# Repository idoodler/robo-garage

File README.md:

# Robo-Garage

Kitchen cabinet garage for a **Dreame L10s Pro Ultra Heat** robot vacuum.
ESP32 + ESPHome + Home Assistant: motorised door, light barrier, reed contacts, fan, LED ring, temperature/humidity, water leak probe + valve, buzzer.

**Live simulator:** https://claude.ai/artifact/KapGY8dMDmhuJijCuEXQXC

## Versions

| Part | Version | Status |
|---|---|---|
| Controller PCB | v1.3.1 | DRC 0 errors / 0 warnings (KiCad 7). JLCPCB assembles all parts (SMD + clamps), only the DevKitC is plugged in (USB-C reachable from outside). Power headroom: 12 V in 6 A, actuator 4.9 A limit, valve 3 A, every power path checked against IPC-2221. v1.3.1: clamp pins in 2 rows like the real part, pick & place rotations computed from JLC's own footprints |
| Case | v1.3.1 | fits PCB v1.3.1 (0 mm³ overlap with the part stand-in), DevKit USB-C through the left wall |
| ESPHome config | – | checked with ESPHome 2026.10.2. Set in HA without reflashing: beam type, actuator type (with / without built-in limit switches), open / close time, motor current threshold, stall current; "Door motor fault" when a move draws no current. Light barrier: retroreflective NPN sensor (E3Z-R61 type, Light-ON) + reflector on the BEAM clamp, blue wire on TX− so the self-test can switch it off (no PCB change). Line LED: SK6812 RGBW 144/m, 72 LEDs, capped at 25 % per channel (≤ 1.44 A of the 1.5 A LED output) |
| Simulator | v5.6 | door open slider for all 4 door types, printed door parts (doors v2.2) in 3D + side view, door downloads, retroreflective light barrier with its reflector, Line LED with 72 SK6812 RGBW LEDs |
| Doors | v2.2 | Printed parts for all 4 door types (lift door, flap out, up & over, parallel lift), no supports. Up & over + parallel lift: print-in-place modules with hourglass joints and hollow pins, skeleton plates and arms checked by 3D FE as printed (`check_strength.py`): 12 % less filament than v2.1 (both module pairs together), the most loaded spot down from 1.35 to 0.87 of its allowable at a 100 N stall (calculated), checked over the whole travel (joint gap 0.45 mm, up & over peg in its track 0.4 mm, other gaps ≥ 1 mm). Parallel lift parks 23 mm out (40 mm max) |

## Folders

| Folder | What is inside |
|---|---|
| `esphome/` | ESPHome config for the board (needs `secrets.yaml` with `wifi_ssid`, `wifi_password`) |
| `homeassistant/` | Home Assistant blueprint `robo-garage.yaml`: door follows the robot vacuum, clean button, button ring + status LED, rear fan drying, iOS Live Activities, messages (see below) |
| `pcb/gen/` | PCB generator (Python + KiCad `pcbnew`). `parts.py` = single source of truth, `fplib.py` makes the own footprints (`pcb/lib/robo.pretty`) |
| `pcb/robo-garage/` | Work folder. Only `robo-garage.ses` (Freerouting result) is in git |
| `pcb/out/` | Order files: gerbers zip, BOM + CPL for JLCPCB, KiCad project, renders, `pin1-check.png`. **Order guide: `pcb/out/README.md`** |
| `case/` | 3D-printed case: OpenSCAD source, STL files, pictures, print guide |
| `doors/` | Printed door parts for all 4 door types: OpenSCAD source, STL files, check scripts, print + assembly guide (`doors/README.md`) |
| `simulator/` | Simulator web page: `robo-garage.html` (source) → `build_page.py` → `index.html` |

## Build

GitHub Actions runs all of this on every push (`.github/workflows/build.yml`).
Locally: run from the repo root. Tested with KiCad 7.0.11 (Python `pcbnew`), Python 3 + shapely 2.2, OpenSCAD 2021.01.

| Step | Command |
|---|---|
| PCB: bare board | `python3 pcb/gen/build.py` |
| PCB: tracks + GND pour + DRC | `python3 pcb/gen/finish.py` (stops with an error on any DRC issue) |
| PCB: gerbers, BOM, CPL, renders | `python3 pcb/gen/fab.py pcb/robo-garage/robo-garage_routed.kicad_pcb pcb/out` |
| PCB: copy to `pcb/out` + zip | `pcb/gen/package.sh` |
| PCB: re-route (optional) | `pcb/gen/pipeline.sh` (Freerouting is not deterministic: run it again if `finish.py` reports unconnected items) |
| Case: PCB data, STL, zip | `case/build.sh` |
| Doors: STL, zip | `doors/build.sh` (other joint gap: `doors/build.sh -D cj=0.35`) |
| Doors: motion, gap and overhang checks | `python3 doors/check_parallel.py`, `python3 doors/check_upover.py`, `python3 doors/check_simple.py` |
| Doors: strength (joint loads + 3D FE as printed, about 6 min on 32 cores, up to 48 GB; `--jobs=1` for less) | `python3 doors/check_strength.py` (misuse case: `--yank`) |
| Simulator page | `python3 simulator/build_files.py` (downloads, pictures, case + door GLB) then `python3 simulator/build_page.py` |
| Flash ESP32 | `esphome run esphome/robo-garage-pcb.yaml` |

| Tool | Needed for |
|---|---|
| Python packages `shapely` 2.2, `segno` 1.6 (QR code on the silkscreen) | `build.py`, `finish.py` |
| `kicad-cli`, `rsvg-convert`, Python package `Pillow` | `fab.py` |
| `zip` | `package.sh`, `case/build.sh`, `doors/build.sh` |
| `openscad`, font DejaVu Sans | `case/build.sh`, `doors/build.sh`, `simulator/build_files.py` |
| Python packages `trimesh`, `rtree`, `shapely`, `numpy`; `xvfb-run` for `render.py`; `scipy`, `pyamg` for `check_strength.py`; `matplotlib` for `paper_template.py` (run by `doors/build.sh`) | `doors/check_*.py`, `doors/render.py`, `doors/paper_template.py` |
| Python packages `Pillow`, `trimesh`, `numpy`, `shapely`, `fast-simplification` | `simulator/build_files.py` |
| Java, `xvfb-run`, `pcb/tools/freerouting-1.9.0.jar` ([Freerouting releases](https://github.com/freerouting/freerouting/releases)) | `pipeline.sh` only |

Moved a part in `parts.py`? Then the old tracks no longer fit: run `pcb/gen/pipeline.sh` and commit the new `pcb/robo-garage/robo-garage.ses`.

## Home Assistant

Blueprint `homeassistant/robo-garage.yaml` (HA 2026.7 or newer). Import it: *Settings → Automations & scenes → Blueprints → Import blueprint*, URL
`https://github.com/idoodler/robo-garage/blob/main/homeassistant/robo-garage.yaml`, then *Create automation* and pick the robot vacuum and the Robo-Garage entities.

| What happens | How |
|---|---|
| Robot leaves the dock or starts returning | door opens; not open within the time limit or a door motor fault → robot paused + message. Dreame mop wash / drying after the job (reports "cleaning" while docked) keeps the door shut |
| Robot back in the dock, job over, for 1 min (set it) | door closes; beam blocked → the controller reopens, the blueprint waits for a clear beam and tries again (3×), then a message. Dreame: waits while the job still runs in the dock (mop washing, recharge) |
| Clean button | robot docked → door opens, then the robot starts (not on a door motor fault). Robot out → sent home (or paused / nothing) |
| Button ring | on while the robot is parked (brightness set it, 0 = off), pulses during a job in the dock, blinks on a problem |
| Status LED (optional) | red strobe = problem, orange chase = door moving, blue bar = job progress ("Progress" effect + "Status LED progress" number), spinner = returning, pulse = washing / charging in the dock, green = done (2 min), dim pulse = mop wash after the job |
| Water leak, beam fault, motor fault, stall, supply low, robot error | message to the notify entities you pick, else a notification in HA |
| Rear fan | after parking (door closed): fan at 60 % for 60 min (set both, 0 % = off), then back to "Vent auto". Stops early when the robot leaves |
| iOS Live Activities (optional, pick the phones; English or German) | cleaning job: a bar per room, current room + %, phase (mop wash, to the station, ...), door opening / closing, then done / stopped / error; outside a job the door status. Problems: one red list of every robot, station and garage problem, "✅ Problem solved" when all are clear. Made for the Dreame integration (task status, state, current room, progress, error, station sensors + a text and a toggle helper) |
| HA or controller restart | door put back where it belongs |
| Optional | close the door while the robot is out (opens again on "returning"); keep the door open while the drawer is out |

The safety work stays in the firmware: beam stop, stall stop, leak valve.

## Release

| Step | What to do |
|---|---|
| 1 | Set the versions: `VERSION` in `pcb/gen/parts.py` (also printed on the board), `version` in `case/robo-garage-case.scad` |
| 2 | Push to `main` → GitHub Actions builds everything and checks the DRC |
| 3 | Push a tag: `git tag v1.3.1 && git push origin v1.3.1` → GitHub Actions publishes the release with both zips |
| or | On github.com: *Releases* → *Draft a new release* → new tag `v1.3.1` → *Publish*. The zips get attached about 2 min later |

Every build also keeps both zips for 30 days: *Actions* → run → *Artifacts*.

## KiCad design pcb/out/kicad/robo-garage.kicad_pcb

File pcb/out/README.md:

# Robo-Garage controller PCB v1.3.1

100 × 100 mm, 2 layers, 1 oz copper, all parts on top. Made with KiCad 7 + Freerouting (FOSS). DRC: 0 errors, 0 warnings, 0 unconnected.
**Every BOM line has an LCSC number (all in stock, checked 3 Nov 2026) → JLCPCB assembles the whole board (SMD + clamps, sockets, fan header). You only plug in the DevKitC.**

**New in v1.3.1: fit + orientation fixes**
| Fix | v1.3 | v1.3.1 |
|---|---|---|
| KF250 clamps (9 ×) | all pins in one row | **2 pin rows 5 mm apart (zig-zag)**, as on the real part (datasheet + JLC footprint). The v1.3 clamps would not have fitted |
| Pick & place rotation | package rules | **computed from JLC's own footprint of each part** (`pcb/gen/jlc_footprints.json`); the build stops if a part fits no rotation |
| Rotation corrected | – | U2, U3 (pin 1 corner), Q6 (90°), C13 (polarity), BZ1 (− lead was on a dummy pad), J6 (latch peg), J3 / J4 / J15 (90°) |
| Fan header J6 peg hole | Ø1.10 (KiCad stock) | **Ø1.25** as on the Molex drawing |

**New in v1.3: power headroom**
| Area | v1.2 | v1.3 |
|---|---|---|
| 12 V input | 3 A, 2-pole clamp, PTC 2.6 A, AO3407A | **6 A**, 4-pole clamp (2 × 12V, 2 × GND), PTC 7 A (2920), P-FET AO4407C (11.5 mΩ), TVS SMAJ15A |
| Actuator | DRV8871, limit 1.9 A | **DRV8874** (6 A peak), current limit **4.9 A** (R5 = 1.5 kΩ), 3 A moves |
| Motor current | 0.1 Ω shunt, INA219 range 3.2 A | 20 mΩ / 2 W shunt with Kelvin taps, INA219 range 8 A |
| Valve | AO3400A, PTC 1.5 A → max 1.2 A | **IRLTS6342** (30 V, 8.3 A), PTC 4 A (1812) → **max 3 A** |
| 12 V aux | direct from the rail | own PTCs: F7 1.1 A (fan, beam, leak), F8 0.2 A (button LED) |
| LED 5 V | PTC 1.5 A | PTC 2 A |
| T/H sensor | SHT40 | SHT41 (same footprint, address 0x44) |
| Copper | 1.0–1.5 mm | every power path checked against IPC-2221 (table below) |

## Limits (also printed on the back)
| Output | Limit | Protection |
|---|---|---|
| 12 V IN | 6 A continuous (board ≤ 40 °C). PSU 12 V / 5 A recommended, a 3 A PSU still works | F1 PTC 7 A hold / 14 A trip, reverse-polarity P-FET, TVS 15 V |
| ACTUATOR | 3 A moving, **4.9 A hardware limit** | DRV8874 current regulation + over-current + thermal shutdown, INA219 stall stop (firmware) |
| VALVE | 12 V, **3 A** continuous, inductive OK | F4 PTC 4 A hold (≈ 3.2 A at 50 °C), SS34 flyback |
| LED 5 V | 1.5 A (16 WS2812 at full white ≈ 1 A; Line: 72 SK6812 RGBW capped at 25 % in ESPHome ≈ 1.44 A) | F2 PTC 2 A |
| 5 V rail total | 3 A | LMR51430 current limit + hiccup |
| FAN + BEAM + LEAK 12 V | 1.1 A together | F7 1.1 A, F3 / F5 0.2 A per sensor feed |
| BUTTON LED 12 V | 0.2 A | F8 0.2 A |
| LEAK 3V3 | 50 mA | F6 0.2 A (shares the DevKit regulator) |
| Clamps | 5 A per pole, 0.2–0.75 mm² | – |

## Copper check (IPC-2221, outer layer, 1 oz)
DC network solve over every track and via of each power net, current = the limit above. Need = IPC-2221 width for ≤ 20 °C rise.
| Path | Current | Copper (narrowest) | Need | Drop |
|---|---|---|---|---|
| 12V IN → F1 → Q1 | 7 A | 3.0 / 4.2 mm | 2.9 mm | 20 mV |
| Q1 → shunt (west trunk) | 4.9 A | 2.0 mm | 1.8 mm | 81 mV |
| Q1 → valve PTC (east branch) | 4 A | 2.0 mm | 1.3 mm | 21 mV |
| Shunt → DRV8874 VM | 4.9 A | 2.0 mm | 1.8 mm | 67 mV |
| DRV8874 → ACTUATOR clamp | 4.9 A | 1.8 mm (spots of 1.5–1.6 mm: M− 12 mm, M+ 4 mm in total) | 1.8 mm | 44 / 66 mV |
| VALVE 12V / VLV | 4 A | 1.5 mm | 1.3 mm | 24 / 15 mV |
| Buck input | 1.5 A | 0.8 mm | 0.4 mm | 29 mV |
| 5 V buck → LED clamp | 2 A | 0.8 mm | 0.5 mm | 90 mV |
| Aux 12 V (fan, beam, leak) | 1.1 A | 0.6 mm | 0.2 mm | 96 mV |
| Vias in power paths | ≤ 1.1 A | 0.4–0.6 mm drill | 1.3 A per via | – |

Pin necks: 0.4–0.6 mm for ≤ 1.4 mm at the 0.65 mm-pitch DRV8874 pins and the buck SW pin (set by the pin pitch; the wide copper starts right after the pad).
At 4.9 A the 1.5 mm spots run ≈ 26 °C above ambient when held for minutes; a door move takes ≤ 15 s and runs at ≈ 3 A (≈ 10 °C).

## Part checks (datasheets)
| Part | Check | OK |
|---|---|---|
| DRV8874PWPR (U1) | VM 4.5–37 V, 6 A peak, 200 mΩ HS+LS. 3 A → 1.8 W for ≤ 15 s per move; a stall at 4.9 A ends in the firmware stall stop or the driver's thermal shutdown | ✓ |
| LMR51430XFDDCR (U4) | 500 kHz FPWM, 4.5–36 V in, 3 A. TI 12 → 5 V example: 6.8 µH + 44 µF → board: 6.8 µH (Isat 6 A) + 3 × 22 µF. EN tied to VIN through 100 k (allowed) | ✓ |
| INA219 (U2) | Bus ≤ 26 V; the TVS keeps surges ≤ 24.4 V | ✓ |
| IRLTS6342 (Q6) | 30 V, 8.3 A, Vgs ±12 V (driven at 3.3 V): 0.2 W at 3 A | ✓ |
| AO4407C (Q1) | 30 V, 14 A, Vgs ±25 V (BZT52C12 clamps it to 12 V): 0.4 W at 6 A | ✓ |
| R6 20 mΩ 2 W | 0.48 W at 4.9 A | ✓ |
| R44 10 Ω 1206 | ≈ 0.19 W while the buzzer sounds (0.25 W part) | ✓ |
| Electrolytics | C1 / C3 25 V on 12 V, C13 16 V on 5 V | ✓ |
| PTCs | voltage rating ≥ rail: F1 24 V, F4 16 V, F3/F5–F8 30 V on 12 V; F2 12 V on 5 V | ✓ |

## Files
| File | Use |
|---|---|
| `robo-garage_gerbers_JLCPCB.zip` | Upload at JLCPCB (PCB) |
| `robo-garage_BOM_JLCPCB.csv`, `robo-garage_CPL_JLCPCB.csv` | PCB Assembly: BOM + pick & place (48 lines, 114 parts) |
| `pin1-check.png` | Cyan ring = our pin 1 / + / cathode, magenta dot = where JLC puts it (its footprint turned by the CPL rotation). Every dot sits in its ring; compare with JLC's placement preview |
| `orientation.txt` | CPL rotation of every polarised part and the JLC footprint it was computed from |
| `robo-garage-pcb.yaml` | ESPHome config for this board |
| `kicad/` | KiCad project to edit later |
| `render_top.png`, `render_bottom.png` | Pictures |

## Order at JLCPCB
| Step | Setting |
|---|---|
| 1 PCB | Upload the gerbers zip → 2 layers, 1.6 mm, LeadFree HASL, **1 oz**, via covering *Tented*, "Mark on PCB": default. The C-shaped slot around the SHT41 (bottom right) is intended (heat isolation): confirm if JLC asks |
| 2 Assembly | **Economic**, top side, 2 boards, **Tooling holes: Added by Customer** (TH1–TH3 are on the board), *Confirm Parts Placement* = yes |
| 3 Files | Upload BOM + CPL. Parts list: all 48 lines must match by LCSC number (0 "no part selected") |
| 4 THT | The clamps, the 3 sockets and the fan header are THT: keep them ticked → JLC solders them (≈ $3.5 + $0.02 per joint, 96 joints per board) |
| 5 Preview | Compare the placement preview with **`pin1-check.png`**: JLC's pin-1 dot / + / cathode mark must sit in the cyan ring of every U, Q, D, LED, C1, C3, C13, BZ1 and J. The CPL already uses JLC's own footprints (`orientation.txt`), so nothing should need turning. Clamps: wire entry towards the board edge. If JLC's engineers ask about polarity (*Confirm Parts Placement*), answer with `pin1-check.png` |
| 6 Price | ≈ 26 "extended" part types (≈ $3 loading fee each, once per order) – normal for a board like this |

Out of stock? U1 → DRV8874QPWPRQ1 (C22448174, same pinout). U5 → SHT40-AD1F-R2 (C7461846) or SHT41-AD1F-R2 (C7461862), same address, with PTFE cap. KF250 clamp → same footprint family DG250-3.5 / WJ250-3.5 (check the drawing: Ø1.2 holes, 3.5 mm pole pitch, 2 pin rows 5.0 mm apart, odd poles 2.2 mm from the rear face), or leave that line out and hand-solder. Any substitute part needs its JLC footprint in `pcb/gen/jlc_footprints.json` (the build says so). PTCs → same size, hold current and at least the same voltage.

## Parts to buy separately
| Part | Qty | Where it goes |
|---|---|---|
| ESP32 DevKitC V4, **WROOM** (not WROVER: GPIO16/17 are used), board 1.1 in (28 mm) or 1.0 in (25.4 mm) wide – not the narrow 0.9 in clone | 1 | Plugs into J3 + J4 (25.4 mm rows) or J3 + J15 (22.86 mm), USB-C to the left board edge |
| Power supply 12 V DC, **5 A** (e.g. Mean Well GST60A12); the 3 A GST36E12 still works for the standard actuator | 1 | 12 V IN clamp (via a DC-jack adapter) |
| Light barrier, 12–24 V DC, **retroreflective** with its reflector, **NPN**, mode switch on **L** (Light-ON), e.g. Omron E3Z-R61 type. Keep Light-ON (HA "Beam type" = Light-ON (NC)): the self-test needs it. A through-beam pair (E3Z-T61 type, NPN) works too, see BEAM below | 1 + reflector | BEAM clamp |
| Leak detection: 2 stainless screws / bare wire ends 5–10 mm apart on the cabinet floor (nothing else needed), **or** a leak sensor with a digital output: NPN / open-collector (12 V or 3.3 V supply, plus a 10 kΩ resistor between the 3V3 and SIG poles) or 3.3–5 V logic module (LM393 type, 3.3 V supply, ≤ 50 mA) | 1 | LEAK clamp |
| Water valve 12 V DC, **≤ 3 A**, that **closes when powered** (normally-open solenoid or motorised ball valve "NO") | 1 | VALVE clamp (optional) |
| VL53L1X module | 1 | I2C clamp (optional) |

## Wiring
| Clamp | Pins (top → bottom / left → right) | Connect |
|---|---|---|
| 12 V IN | +12V, +12V, GND, GND | 12 V adapter → DC-jack adapter. Up to 5 A one +12V + one GND is enough, above 5 A use both pairs |
| ACTUATOR | M+, M− | Actuator (≤ 4.9 A). Door moves the wrong way → swap the 2 wires |
| FAN | 4-pin header | ARCTIC P12 Slim PWM plug |
| LED | 5V, DAT, GND | SK6812 RGBW line (72 LEDs) or WS2812B strip / ring (DIN) |
| BUTTON | BTN, GND, 12V, LED− | Alu button: NO, C, LED+, LED− |
| REEDS | CL/GND, OP/GND, DR/GND | Door closed, door open, drawer reed |
| BEAM (left) | RX+, RX−, SIG, TX+, TX−, GND | Retroreflective sensor: brown → RX+, black → SIG, **blue → TX−** (the self-test switches the sensor off there); RX−, TX+, GND stay free. Through-beam pair instead: receiver brown, blue, black → RX+, RX−, SIG; emitter brown, blue → TX+, TX−. Beam across the cabinet front, ≈ 12 cm in front of the door, ≈ 2 cm above the floor |
| LEAK (left) | 3V3, SIG, GND, 12V | Electrodes: SIG + GND (no polarity). Digital sensor: VCC → 3V3 (≤ 50 mA) or 12V, OUT → SIG (0–5 V only, never 12 V), GND; NPN / open collector: 10 kΩ between 3V3 and SIG. Wet = SIG low (NPN / active-low); active-high sensor → `leak_inverted: "true"` |
| VALVE (right) | 12V, VLV | Valve + → 12V, valve − → VLV (low side, flyback diode on board), ≤ 3 A |
| I2C ToF | 3V3, SDA, SCL, GND | VL53L1X module (optional) |

**Clamps:** push the button with a 2.5 mm screwdriver, insert the stripped wire (6–7 mm, 0.2–0.75 mm², ferrules OK) at 45° from the board edge, release.

## Pins (ESP32)
| GPIO | Function |
|---|---|
| 25 / 26 | DRV8874 IN1 (open) / IN2 (close), PWM mode |
| 32 / 33 / 18 | Reed door closed / door open / drawer |
| 19 | Clean button |
| 23 | Button ring (AO3400A, 12 V) |
| 16 | LED strip data (74AHCT1G125 → 330 Ω) |
| 17 / 27 | Fan PWM (2N7002, inverted) / fan tach |
| 21 / 22 | I²C SDA / SCL (INA219 0x40 + SHT41 0x44 on board, VL53L1X on the clamp) |
| 34 | Light barrier input (via 2N7002, 12 V safe) |
| 13 | Light barrier self-test: switches the sensor (or the emitter) off via TX− (AO3400A) |
| 4 / 35 | Leak drive (pulsed 3.3 V through 100 k) / leak ADC (BAT54S clamp) |
| 2 | Valve (IRLTS6342 low side, 10 k pull-down: off at boot) |
| 15 | Buzzer (AO3400A, 10 k pull-down: off at boot) |
| 36 (VP) | 12 V rail ADC (100k / 22k, BAT54S clamp) |
| 14, 5, 39 (VN) | Spare on the EXP header J11 (not assembled); 39 = input only |

## Sensors, safety, alarms
| Item | How it works |
|---|---|
| Leak | Every 10 s IO4 drives 3.3 V through 100 k for 70 ms, IO35 reads SIG (dry electrodes ≈ 3.1 V, a digital sensor 0 V / 3.3 V). 3 wet readings in a row (25 s) → "Water leak" on, valve powered, red strobe, beep. Water gone → LED off after 60 s; **the valve stays powered until you switch it off in HA**. Tap water between two screws 5–10 mm apart reads well below 1 V; only very clean water (< 200 kΩ needed) could stay above the 2.2 V threshold → raise `leak_threshold` to 2.8 then. |
| Valve | Use a valve that closes when powered: a cut wire or a dead PSU cannot shut the water, but a leak does. F4 (4 A / 16 V PTC) protects the output. |
| Buzzer | Alerts in ESPHome via `rtttl.play`. "Buzzer" switch off → everything except the leak alarm is silent. |
| 12 V rail | "12 V rail" sensor (±0.3 V) and "Supply voltage low" when it sags below `supply_low` (weak PSU, stalled actuator). |
| SHT41 | Own island + vented case chamber → cabinet air. Set `offset` in the YAML after a check. Humidity can read low for 1–2 days after soldering. |
| Auto vent | Fan on above 65 %RH / 30 °C (HA numbers), 30–100 % speed; off 5 %RH / 1 °C below, and while the drawer is out. Set "Rear fan" (on / off / speed) by hand in HA → "Vent auto" switches off and your setting stays; switch "Vent auto" on again to resume. |
| Light barrier | Door does not close while the beam is blocked; broken while closing → stop + reopen. Self-test before every close and every 10 min (sensor off via TX−: the input must read "blocked") → "Door beam fault". Receiver type: HA "Beam type" (beam clear → "Door beam" must show "Clear", else pick the other type). "None" = no light barrier: no check, no self-test, the door closes without the safety stop. |
| Actuator type | HA "Actuator type": **No limit switches** (default) = the door stops at the reeds, on a stall, or after "Open time" / "Close time" (HA, default 15 s). **Built-in limit switches** = the actuator cuts its own power at each end; current below "Motor current threshold" (HA, default 0.02 A) for 0.3 s counts as that end reached, so the reeds are optional. Every move must draw more than the threshold within 1.5 s, else the door stops and "Door motor fault" turns on (driver, J5 wiring or actuator). Tune the threshold between the idle and running current shown in "Door motor current". |
| Stall stop | INA219 motor current > "Stall current" (HA, default 0.8 A) for 0.4 s → stop. Set it ≈ 0.3 A above the running current under load ("Door motor current"). |

## Power
12 V in (6 A) → PTC 7 A → reverse-polarity P-FET → TVS 15 V → three branches: actuator (shunt → DRV8874, 4.9 A limit), valve (PTC 4 A), aux 12 V (PTC 1.1 A: fan, beam, leak; PTC 0.2 A: button LED). LMR51430 buck makes 5.1 V (3 A max) for the ESP32 (via Schottky, USB can stay plugged in), the LEDs (PTC 2 A) and the buzzer.

| PSU sizing (12 V side) | Current |
|---|---|
| Actuator (running) | as measured, e.g. 1.5 A (board limit 4.9 A) |
| Valve | as rated, e.g. 0.5 A (board limit 3 A) |
| 5 V side (ESP32 + 16 LEDs full white + buzzer) | ≈ 0.6 A |
| Fan + beam + button LED | ≈ 0.3 A |
| **Sum** | standard parts ≈ 3 A → 12 V / 5 A PSU; the board itself takes up to 6 A |

Keep LED brightness low (full white on all LEDs heats the buck).

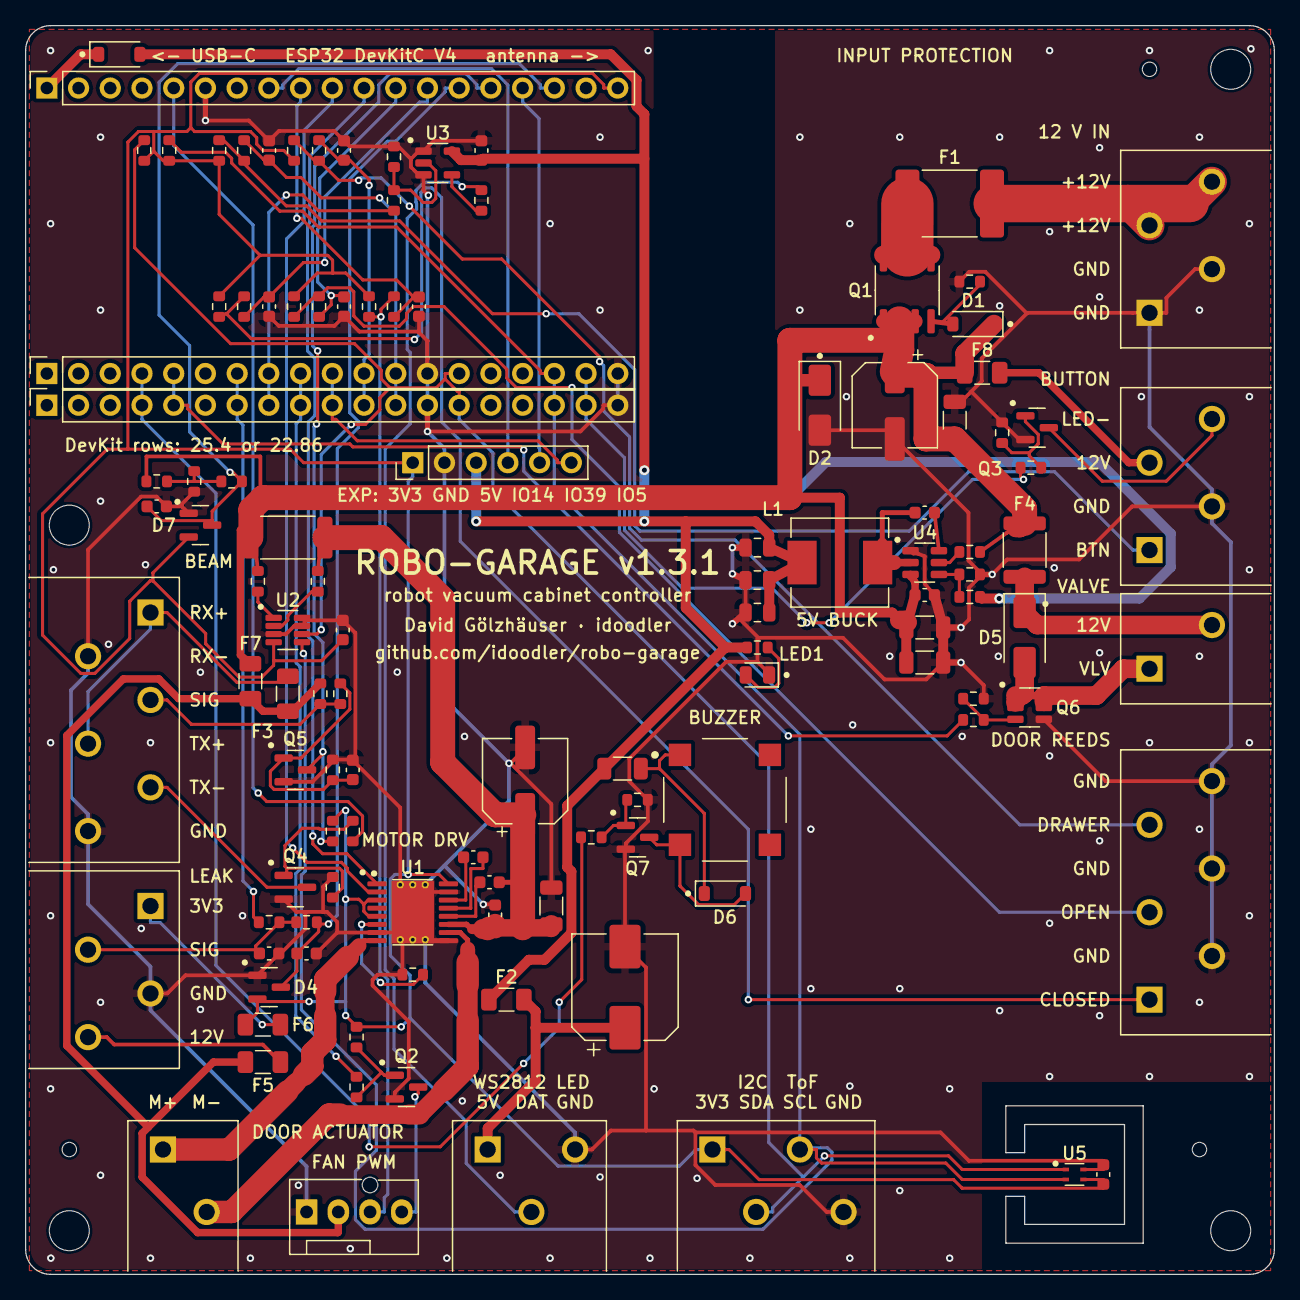
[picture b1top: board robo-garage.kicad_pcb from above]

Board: 2 copper layers, 100.0 x 100.0 mm, 122 parts (0 on the bottom side), 74 nets.

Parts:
BZ1: MLT-8530; Buzzer_SMD_MLT-8530_8.5x8.5mm
C1, C3: 100uF 25V; CP_Elec_6.3x7.7
C2, C10, C22, C23: 10uF 50V; C_1206_3216Metric
C9, C11, C12, C16, C17, C18, C19, C20, C21, C28, C31, C32, C33: 100nF; C_0603_1608Metric
C13: 470uF 16V; CP_Elec_8x10
C15, C27, C30: 1nF; C_0603_1608Metric
C24, C25, C26: 22uF 25V; C_0805_2012Metric
C34: 22nF; C_0603_1608Metric
D1: BZT52C12; D_SOD-123
D2: SMAJ15A; D_SMA
D3, D6: B5819W; D_SOD-123
D4, D7: BAT54S; SOT-23
D5: SS34; D_SMA
F1: PTC 7A 24V; Fuse_2920_7451Metric
F2: PTC 2A 12V; Fuse_1206_3216Metric
F3, F5, F6, F8: PTC 200mA 30V; Fuse_1206_3216Metric
F4: PTC 4A 16V; Fuse_1812_4532Metric
F7: PTC 1.1A 30V; Fuse_1206_3216Metric
H1, H2, H3, H4: M3; MountingHole_3.2mm_M3
J2: 12V IN; KF250-3.5-4P_1x04_P3.50mm_45Degree
J3: DevKitC socket (5V..3V3); PinSocket_1x19_P2.54mm_Vertical_Tight
J4: DevKitC socket (CLK..GND) outer 25.4; PinSocket_1x19_P2.54mm_Vertical_Tight
J5: ACTUATOR; KF250-3.5-2P_1x02_P3.50mm_45Degree
J6: Fan 4-pin; FanPinHeader_1x04_P2.54mm_Vertical
J7: LED; KF250-3.5-3P_1x03_P3.50mm_45Degree
J8: BUTTON; KF250-3.5-4P_1x04_P3.50mm_45Degree
J9: REEDS; KF250-3.5-6P_1x06_P3.50mm_45Degree
J10: I2C; KF250-3.5-4P_1x04_P3.50mm_45Degree
J11: EXP (optional); PinHeader_1x06_P2.54mm_Vertical
J12: BEAM; KF250-3.5-6P_1x06_P3.50mm_45Degree
J13: LEAK; KF250-3.5-4P_1x04_P3.50mm_45Degree
J14: VALVE; KF250-3.5-2P_1x02_P3.50mm_45Degree
J15: DevKitC socket (CLK..GND) inner 22.86; PinSocket_1x19_P2.54mm_Vertical_Tight
L1: 6.8uH 6A; L_Chilisin_BMRx00060630
LED1: green; LED_0805_2012Metric
Q1: AO4407C; SOIC-8_3.9x4.9mm_P1.27mm
Q2, Q5: 2N7002; SOT-23
Q3, Q4, Q7: AO3400A; SOT-23
Q6: IRLTS6342; SOT-23-6
R1, R16, R27, R34, R40, R47: 100k; R_0603_1608Metric
R4: 2.2k; R_0603_1608Metric
R5: 1.5k; R_0603_1608Metric
R6: 20m 2W; R_2512_6332Metric
R7, R8, R31: 4.7k; R_0603_1608Metric
R9: 330; R_0603_1608Metric
R10, R12, R13, R17, R19, R20, R21, R26, R32, R35, R36, R41, R43, R46, R49: 10k; R_0603_1608Metric
R11, R15, R33, R42, R45: 100; R_0603_1608Metric
R14, R18, R22, R23, R24, R30: 1k; R_0603_1608Metric
R25: 75k; R_0603_1608Metric
R28, R29: 0R; R_0603_1608Metric
R44: 10 1206; R_1206_3216Metric
R48: 22k; R_0603_1608Metric
TH1, TH2, TH3: tooling; ToolingHole_JLCPCB_1.152mm
U1: DRV8874PWPR; TI_PWP0016J_HTSSOP-16_ThermalVias
U2: INA219AIDCNR; SOT-23-8
U3: SN74AHCT1G125DBVR; SOT-23-5
U4: LMR51430XFDDCR; TSOT-23-6
U5: SHT41-AD1B; Sensirion_DFN-4_1.5x1.5mm_P0.8mm_SHT4x_NoCentralPad

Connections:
+3V3: C11.1, C28.1, D4.2, D7.2, F6.1, J3.19, J10.1, J11.1, R7.1, R8.1, R12.2, R13.2, R17.1, R19.2, R20.2, R21.1, R36.2, U1.3, U1.5, U1.16, U2.4, U5.3
+3V3_LK: F6.2, J13.1
+5V: C12.1, C24.2, C25.2, C26.2, D3.2, F2.1, J11.3, L1.1, R4.1, R25.2, R44.1, U3.5
+5V_DEV: D3.1, J3.1
+5V_LED: C13.1, F2.2, J7.1
+12V: C1.1, C2.1, C21.1, C22.1, C23.1, D1.1, D2.1, F4.1, F7.1, F8.1, Q1.1, Q1.2, Q1.3, R6.1, R27.2, R28.1, R47.1, U4.3
+12V_A: F3.1, F5.1, F7.2, J6.2, R31.2
+12V_BTN: F8.2, J8.3
+12V_F: F1.2, Q1.5, Q1.6, Q1.7, Q1.8
+12V_IN: F1.1, J2.3, J2.4
+12V_LK: F5.2, J13.4
+12V_MOT: C3.1, C9.1, C10.1, C33.2, R6.2, R29.1, U1.11
+12V_VLV: D5.1, F4.2, J14.2
BEAM_12V: F3.2, J12.1, J12.4
BEAM_SIG: J12.3, R31.1, R32.1
BEAM_TX: J12.5, Q4.3
BTN: J8.1, R17.2, R18.1
BZ_K: BZ1.2, D6.2, Q7.3
BZ_P: BZ1.1, D6.1, R44.2
CB: C20.2, U4.6
CPH: C34.2, U1.13
CPL: C34.1, U1.14
EN: R27.1, U4.5
FAN_PWM: J6.4, Q2.3
FAN_TACH: J6.3, R13.1, R14.2
FB: R25.1, R26.1, U4.4
GND: C1.2, C2.2, C3.2, C9.2, C10.2, C11.2, C12.2, C13.2, C15.1, C16.2, C17.1, C18.1, C19.2, C21.2, C22.2, C23.2, C24.1, C25.1, C26.1, C27.2, C28.2, C30.2, C31.2, C32.2, D2.2, D4.1, D7.1, J2.1, J2.2, J3.6, J4.13, J4.19, J6.1, J7.3, J8.2, J9.2, J9.4, J9.6, J10.4, J11.2, J12.2, J12.6, J13.3, J15.13, J15.19, LED1.1, Q2.2, Q3.2, Q4.2, Q5.2, Q6.4, Q7.2, R1.1, R5.1, R10.2, R16.2, R26.2, R34.2, R35.2, R43.2, R46.2, R48.2, U1.7, U1.9, U1.15, U1.17, U2.3, U2.7, U2.8, U3.1, U3.3, U4.1, U5.4
IO2: J4.5, J15.5, R42.1
IO4: J4.7, J15.7, R40.1
IO5: J4.10, J11.6, J15.10
IO13: J3.5, R33.1
IO14: J3.8, J11.4
IO15: J4.4, J15.4, R45.1
IO16: J4.8, J15.8, R30.1
IO17: J4.9, J15.9, R11.2
IO18: C19.1, J4.11, J15.11, R24.2
IO19: C16.1, J4.12, J15.12, R18.2
IO21: J4.14, J10.2, J15.14, R7.2, U2.6, U5.1
IO22: J4.17, J10.3, J15.17, R8.2, U2.5, U5.2
IO23: J4.18, J15.18, R15.1
IO25: J3.11, U1.1
IO26: J3.10, U1.2
IO27: C15.2, J3.9, R14.1
IO32: C17.2, J3.13, R22.1
IO33: C18.2, J3.12, R23.1
IO34: J3.15, Q5.3, R36.1
IO35: C31.1, D4.3, J3.14, R41.2
IPROPI: R5.2, U1.6
ISNS_N: R29.2, U2.2
ISNS_P: R28.2, U2.1
LEAK_S: C30.1, J13.2, R40.2, R41.1
LED_BUF: R9.1, U3.4
LED_DATA: J7.2, R9.2
LED_IN: R10.1, R30.2, U3.2
LED_PWR: LED1.2, R4.2
MOT_A: J5.1, U1.8
MOT_B: J5.2, U1.10
Q1_G: D1.2, Q1.4, R1.2
Q2_G: Q2.1, R11.1, R12.1
Q3_G: Q3.1, R15.2, R16.1
Q4_G: Q4.1, R33.2, R34.1
Q5_G: C27.1, Q5.1, R32.2, R35.1
Q6_G: Q6.3, R42.2, R43.1
Q7_G: Q7.1, R45.2, R46.1
REED_CL: J9.1, R19.1, R22.2
REED_DR: J9.5, R21.2, R24.1
REED_OP: J9.3, R20.1, R23.2
RING_K: J8.4, Q3.3
SW: C20.1, L1.2, U4.2
VALVE_K: D5.2, J14.1, Q6.1, Q6.2, Q6.5, Q6.6
VCP: C33.1, U1.12
VMON: R47.2, R48.1, R49.1
VN: J3.16, J11.5
VP: C32.1, D7.3, J3.17, R49.2

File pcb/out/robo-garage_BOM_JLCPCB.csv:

Comment,Designator,Footprint,LCSC Part #,MPN,Mount
MLT-8530,BZ1,Buzzer_SMD_MLT-8530_8.5x8.5mm,C94599,MLT-8530,SMD
100uF 25V,"C1,C3",CP_Elec_6.3x7.7,C3338,RVT1E101M0607,SMD
10uF 50V,"C2,C10,C22,C23",C_1206_3216Metric,C13585,,SMD
100nF,"C9,C11,C12,C16,C17,C18,C19,C20,C21,C28,C31,C32,C33",C_0603_1608Metric,C14663,,SMD
470uF 16V,C13,CP_Elec_8x10,C970706,RVT1C471M0810,SMD
1nF,"C15,C27,C30",C_0603_1608Metric,C1588,,SMD
22uF 25V,"C24,C25,C26",C_0805_2012Metric,C45783,,SMD
22nF,C34,C_0603_1608Metric,C21122,,SMD
BZT52C12,D1,D_SOD-123,C43491,BZT52C12,SMD
SMAJ15A,D2,D_SMA,C148216,SMAJ15A,SMD
B5819W,"D3,D6",D_SOD-123,C8598,B5819W,SMD
BAT54S,"D4,D7",SOT-23,C408389,BAT54S,SMD
SS34,D5,D_SMA,C8678,SS34,SMD
PTC 7A 24V,F1,Fuse_2920_7451Metric,C495361,SMD2920P700SLR/24,SMD
PTC 2A 12V,F2,Fuse_1206_3216Metric,C883135,BSMD1206-200-12V,SMD
PTC 200mA 30V,"F3,F5,F6,F8",Fuse_1206_3216Metric,C883118,BSMD1206-020-30V,SMD
PTC 4A 16V,F4,Fuse_1812_4532Metric,C47263807,BSMD1812-400-16V,SMD
PTC 1.1A 30V,F7,Fuse_1206_3216Metric,C21714343,BSMD1206-110-30V,SMD
KF250-3.5-4P-1,"J2,J8,J10,J13",KF250-3.5-4P_1x04_P3.50mm_45Degree,C475156,KF250-3.5-4P-1,THT
KH-2.54FH-1X19P-H8.5,"J3,J4,J15",PinSocket_1x19_P2.54mm_Vertical_Tight,C2932678,KH-2.54FH-1X19P-H8.5,THT
KF250-3.5-2P-1,"J5,J14",KF250-3.5-2P_1x02_P3.50mm_45Degree,C475154,KF250-3.5-2P-1,THT
Molex 47053-1000,J6,FanPinHeader_1x04_P2.54mm_Vertical,C240840,Molex 47053-1000,THT
KF250-3.5-3P-1,J7,KF250-3.5-3P_1x03_P3.50mm_45Degree,C475155,KF250-3.5-3P-1,THT
KF250-3.5-6P-1,"J9,J12",KF250-3.5-6P_1x06_P3.50mm_45Degree,C475158,KF250-3.5-6P-1,THT
6.8uH 6A,L1,L_Chilisin_BMRx00060630,C167221,FXL0630-6R8-M,SMD
green,LED1,LED_0805_2012Metric,C2297,KT-0805G,SMD
AO4407C,Q1,SOIC-8_3.9x4.9mm_P1.27mm,C469397,AO4407C,SMD
2N7002,"Q2,Q5",SOT-23,C8545,2N7002,SMD
AO3400A,"Q3,Q4,Q7",SOT-23,C20917,AO3400A,SMD
IRLTS6342,Q6,SOT-23-6,C152628,IRLTS6342TRPBF,SMD
100k,"R1,R16,R27,R34,R40,R47",R_0603_1608Metric,C25803,,SMD
2.2k,R4,R_0603_1608Metric,C4190,,SMD
1.5k,R5,R_0603_1608Metric,C22843,,SMD
20m 2W,R6,R_2512_6332Metric,C160589,RLP25FEER020,SMD
4.7k,"R7,R8,R31",R_0603_1608Metric,C23162,,SMD
330,R9,R_0603_1608Metric,C23138,,SMD
10k,"R10,R12,R13,R17,R19,R20,R21,R26,R32,R35,R36,R41,R43,R46,R49",R_0603_1608Metric,C25804,,SMD
100,"R11,R15,R33,R42,R45",R_0603_1608Metric,C22775,,SMD
1k,"R14,R18,R22,R23,R24,R30",R_0603_1608Metric,C21190,,SMD
75k,R25,R_0603_1608Metric,C23242,,SMD
0R,"R28,R29",R_0603_1608Metric,C21189,,SMD
10 1206,R44,R_1206_3216Metric,C17903,,SMD
22k,R48,R_0603_1608Metric,C31850,,SMD
DRV8874PWPR,U1,TI_PWP0016J_HTSSOP-16_ThermalVias,C1855818,DRV8874PWPR,SMD
INA219AIDCNR,U2,SOT-23-8,C87469,INA219AIDCNR,SMD
SN74AHCT1G125DBVR,U3,SOT-23-5,C7484,SN74AHCT1G125DBVR,SMD
LMR51430XFDDCR,U4,TSOT-23-6,C5219260,LMR51430XFDDCR,SMD
SHT41-AD1B,U5,Sensirion_DFN-4_1.5x1.5mm_P0.8mm_SHT4x_NoCentralPad,C7461861,SHT41-AD1B-R2,SMD
